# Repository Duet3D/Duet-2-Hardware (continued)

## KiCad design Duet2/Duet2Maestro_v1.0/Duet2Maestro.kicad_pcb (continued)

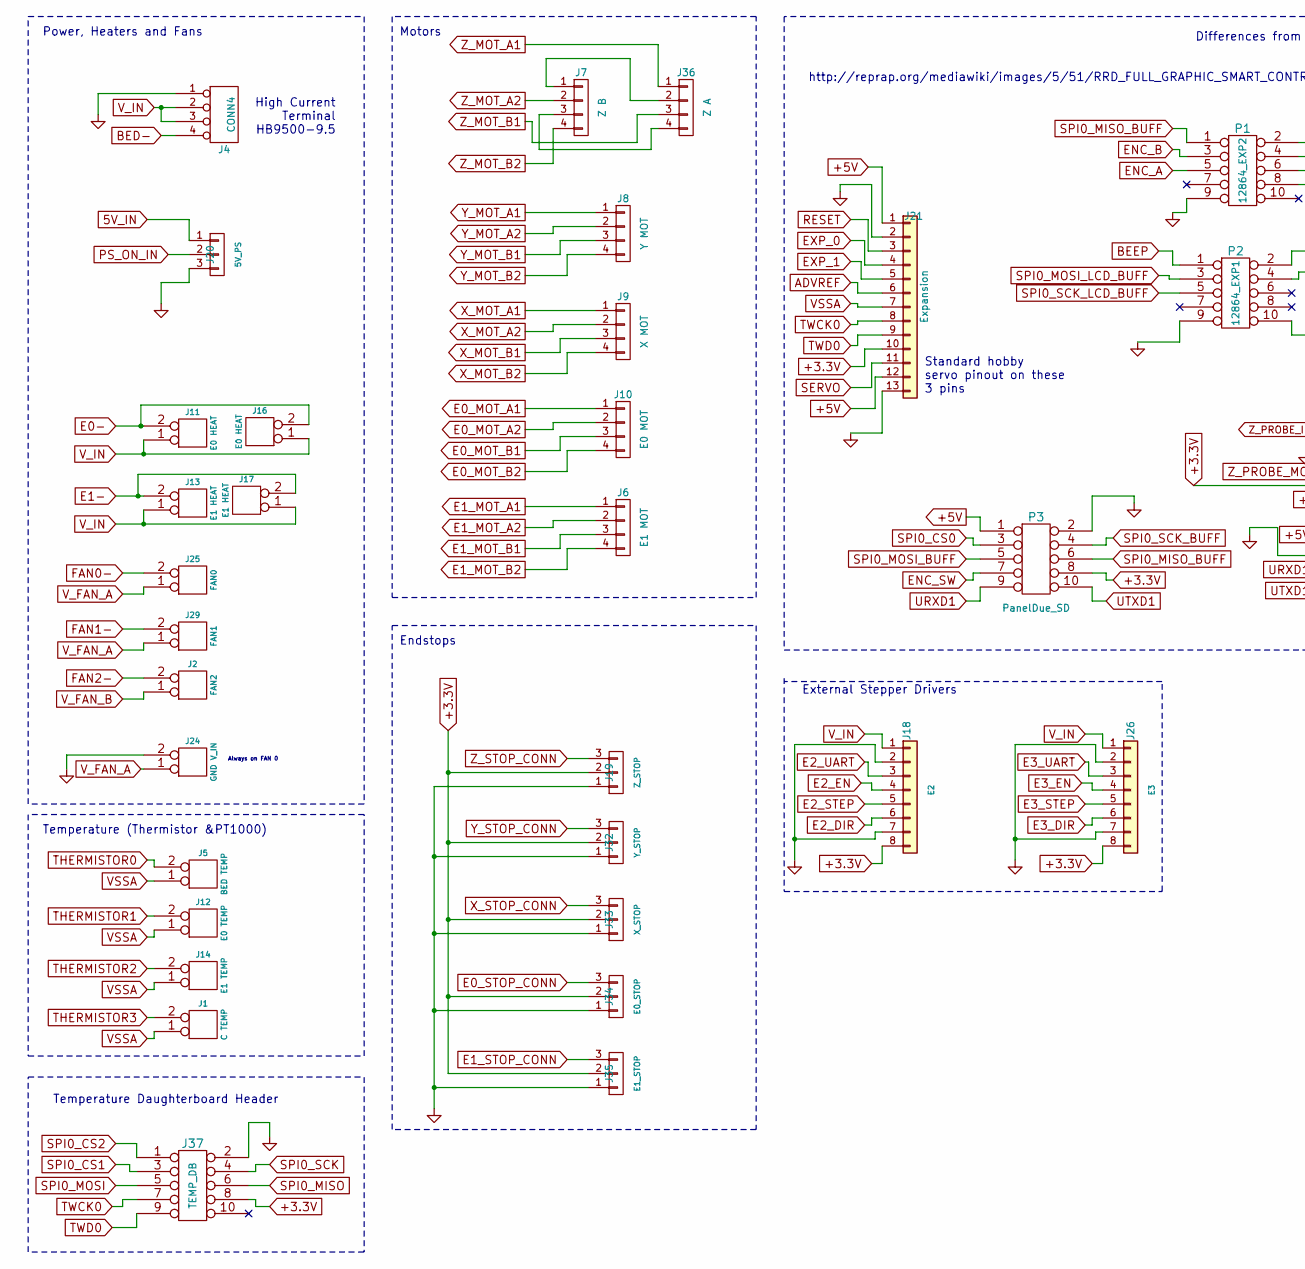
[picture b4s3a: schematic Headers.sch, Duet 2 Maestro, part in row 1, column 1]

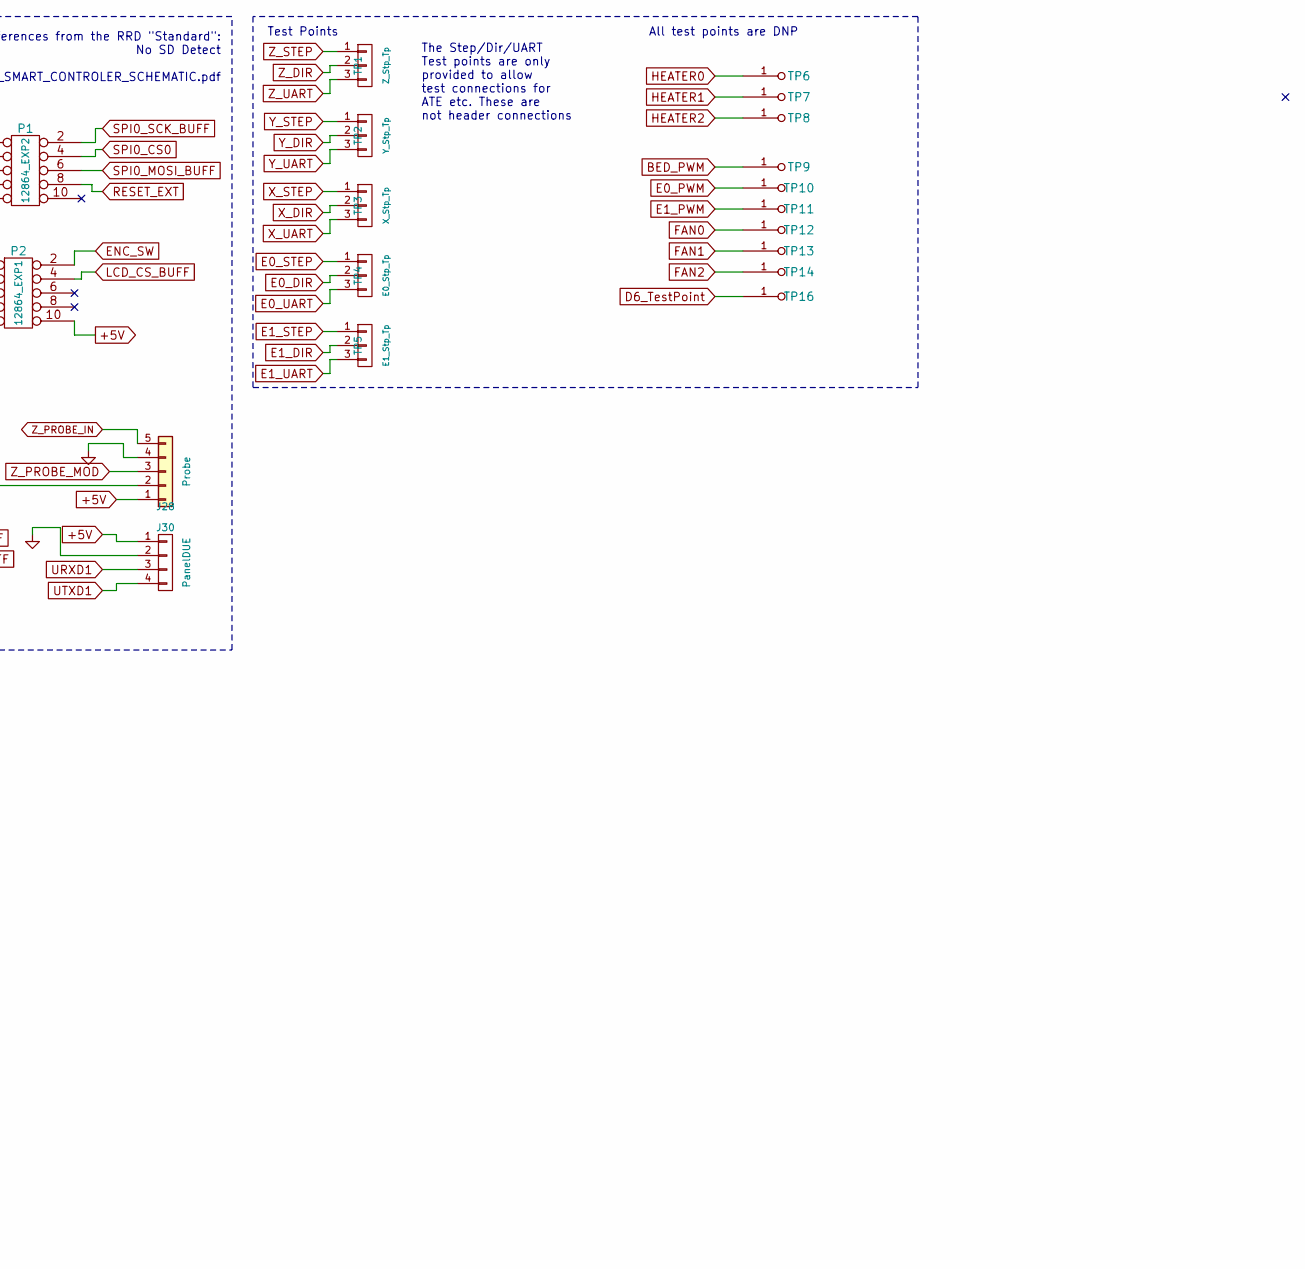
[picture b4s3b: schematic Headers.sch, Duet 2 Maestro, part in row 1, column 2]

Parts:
J1: C TEMP; PIN_ARRAY_2X1
J2: FAN2; PIN_ARRAY_2X1
J4: CONN4; screwt-barrier-9.5mm-1x4
J5: BED TEMP; PIN_ARRAY_2X1
J6: E1 MOT; PIN_ARRAY_4x1
J7: Z B; PIN_ARRAY_4x1
J8: Y MOT; PIN_ARRAY_4x1
J9: X MOT; PIN_ARRAY_4x1
J10: E0 MOT; PIN_ARRAY_4x1
J11: E0 HEAT; 3.5MM_2X1
J12: E0 TEMP; PIN_ARRAY_2X1
J13: E1 HEAT; 3.5MM_2X1
J14: E1 TEMP; PIN_ARRAY_2X1
J16: E0 HEAT; PIN_ARRAY_2X1
J17: E1 HEAT; PIN_ARRAY_2X1
J18: E2; PIN_ARRAY_8x1
J19: Z_STOP; PIN_ARRAY_3X1
J20: 5V_PS; PIN_ARRAY_3X1
J21: Expansion; Pin_Header_Straight_1x13_Pitch2.54mm
J24: GND V_IN; PIN_ARRAY_2X1
J25: FAN0; PIN_ARRAY_2X1
J26: E3; PIN_ARRAY_8x1
J28: Probe; PIN_ARRAY_5x1
J29: FAN1; PIN_ARRAY_2X1
J30: PanelDUE; PIN_ARRAY_4x1
J32: Y_STOP; PIN_ARRAY_3X1
J33: X_STOP; PIN_ARRAY_3X1
J34: E0_STOP; PIN_ARRAY_3X1
J35: E1_STOP; PIN_ARRAY_3X1
J36: Z A; PIN_ARRAY_4x1
J37: TEMP_DB; MAX_TEMP_DB
P1: 12864_EXP2; IDC_PIN_ARRAY_5x2
P2: 12864_EXP1; IDC_PIN_ARRAY_5x2
P3: PanelDue_SD; IDC_PIN_ARRAY_5x2
TP1: Z_Stp_Tp; TPx3
TP2: Y_Stp_Tp; TPx3
TP3: X_Stp_Tp; TPx3
TP4: E0_Stp_Tp; TPx3
TP5: E1_Stp_Tp; TPx3
TP6, TP7, TP8, TP9, TP10, TP11, TP12, TP13, TP14, TP16: TP; TP_via

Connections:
5V_IN: J20.1; also elsewhere on the board
+3.3V: J18.8, J19.2, J21.10, J26.8, J28.2, J32.2, J33.2, J34.2, J35.2, J37.8, P3.8; also elsewhere on the board
+5V: J21.1, J21.12, J28.1, J30.1, P2.10, P3.1; also elsewhere on the board
ADVREF: J21.6; also elsewhere on the board
BED-: J4.4; also elsewhere on the board
BED_PWM: TP9.1; also elsewhere on the board
BEEP: P2.1; also elsewhere on the board
D6_TestPoint: TP16.1; also elsewhere on the board
E0-: J11.2 (PM), J16.2 (PM); also elsewhere on the board
E0_DIR: TP4.2; also elsewhere on the board
E0_MOT_A1: J10.1; also elsewhere on the board
E0_MOT_A2: J10.2; also elsewhere on the board
E0_MOT_B1: J10.3; also elsewhere on the board
E0_MOT_B2: J10.4; also elsewhere on the board
E0_PWM: TP10.1; also elsewhere on the board
E0_STEP: TP4.1; also elsewhere on the board
E0_STOP_CONN: J34.3; also elsewhere on the board
E0_UART: TP4.3; also elsewhere on the board
E1-: J13.2 (PM), J17.2 (PM); also elsewhere on the board
E1_DIR: TP5.2; also elsewhere on the board
E1_MOT_A1: J6.1; also elsewhere on the board
E1_MOT_A2: J6.2; also elsewhere on the board
E1_MOT_B1: J6.3; also elsewhere on the board
E1_MOT_B2: J6.4; also elsewhere on the board
E1_PWM: TP11.1; also elsewhere on the board
E1_STEP: TP5.1; also elsewhere on the board
E1_STOP_CONN: J35.3; also elsewhere on the board
E1_UART: TP5.3; also elsewhere on the board
E2_DIR: J18.6; also elsewhere on the board
E2_EN: J18.4; also elsewhere on the board
E2_STEP: J18.5; also elsewhere on the board
E2_UART: J18.3; also elsewhere on the board
E3_DIR: J26.6; also elsewhere on the board
E3_EN: J26.4; also elsewhere on the board
E3_STEP: J26.5; also elsewhere on the board
E3_UART: J26.3; also elsewhere on the board
ENC_A: P1.5; also elsewhere on the board
ENC_B: P1.3; also elsewhere on the board
ENC_SW: P2.2, P3.7; also elsewhere on the board
EXP_0: J21.4; also elsewhere on the board
EXP_1: J21.5; also elsewhere on the board
FAN0: TP12.1; also elsewhere on the board
FAN0-: J25.2 (PM); also elsewhere on the board
FAN1: TP13.1; also elsewhere on the board
FAN1-: J29.2 (PM); also elsewhere on the board
FAN2: TP14.1; also elsewhere on the board
FAN2-: J2.2 (PM); also elsewhere on the board
GND: J4.1, J18.2, J18.7, J19.1, J20.3, J21.2, J21.13, J24.2 (PM), J26.2, J26.7, J28.4, J30.2, J32.1, J33.1, J34.1, J35.1, J37.2, P1.9, P2.9, P3.2; also elsewhere on the board
HEATER0: TP6.1; also elsewhere on the board
HEATER1: TP7.1; also elsewhere on the board
HEATER2: TP8.1; also elsewhere on the board
LCD_CS_BUFF: P2.4; also elsewhere on the board
unnamed: J7.1, J36.2
unnamed: J7.3, J36.4
PS_ON_IN: J20.2; also elsewhere on the board
RESET: J21.3; also elsewhere on the board
RESET_EXT: P1.8; also elsewhere on the board
SERVO: J21.11; also elsewhere on the board
SPI0_CS0: P1.4, P3.3; also elsewhere on the board
SPI0_CS1: J37.3; also elsewhere on the board
SPI0_CS2: J37.1; also elsewhere on the board
SPI0_MISO: J37.6; also elsewhere on the board
SPI0_MISO_BUFF: P1.1, P3.6; also elsewhere on the board
SPI0_MOSI: J37.5; also elsewhere on the board
SPI0_MOSI_BUFF: P1.6, P3.5; also elsewhere on the board
SPI0_MOSI_LCD_BUFF: P2.3; also elsewhere on the board
SPI0_SCK: J37.4; also elsewhere on the board
SPI0_SCK_BUFF: P1.2, P3.4; also elsewhere on the board
SPI0_SCK_LCD_BUFF: P2.5; also elsewhere on the board
THERMISTOR0: J5.2 (PM); also elsewhere on the board
THERMISTOR1: J12.2 (PM); also elsewhere on the board
THERMISTOR2: J14.2 (PM); also elsewhere on the board
THERMISTOR3: J1.2 (PM); also elsewhere on the board
TWCK0: J21.8, J37.7; also elsewhere on the board
TWD0: J21.9, J37.9; also elsewhere on the board
URXD1: J30.3, P3.9; also elsewhere on the board
UTXD1: J30.4, P3.10; also elsewhere on the board
VSSA: J1.1, J5.1, J12.1, J14.1, J21.7; also elsewhere on the board
V_FAN_A: J24.1, J25.1, J29.1; also elsewhere on the board
V_FAN_B: J2.1; also elsewhere on the board
V_IN: J4.2, J4.3, J11.1, J13.1, J16.1, J17.1, J18.1, J26.1; also elsewhere on the board
X_DIR: TP3.2; also elsewhere on the board
X_MOT_A1: J9.1; also elsewhere on the board
X_MOT_A2: J9.2; also elsewhere on the board
X_MOT_B1: J9.3; also elsewhere on the board
X_MOT_B2: J9.4; also elsewhere on the board
X_STEP: TP3.1; also elsewhere on the board
X_STOP_CONN: J33.3; also elsewhere on the board
X_UART: TP3.3; also elsewhere on the board
Y_DIR: TP2.2; also elsewhere on the board
Y_MOT_A1: J8.1; also elsewhere on the board
Y_MOT_A2: J8.2; also elsewhere on the board
Y_MOT_B1: J8.3; also elsewhere on the board
Y_MOT_B2: J8.4; also elsewhere on the board
Y_STEP: TP2.1; also elsewhere on the board
Y_STOP_CONN: J32.3; also elsewhere on the board
Y_UART: TP2.3; also elsewhere on the board
Z_DIR: TP1.2; also elsewhere on the board
Z_MOT_A1: J36.1; also elsewhere on the board
Z_MOT_A2: J7.2; also elsewhere on the board
Z_MOT_B1: J36.3; also elsewhere on the board
Z_MOT_B2: J7.4; also elsewhere on the board
Z_PROBE_IN: J28.5; also elsewhere on the board
Z_PROBE_MOD: J28.3; also elsewhere on the board
Z_STEP: TP1.1; also elsewhere on the board
Z_STOP_CONN: J19.3; also elsewhere on the board
Z_UART: TP1.3; also elsewhere on the board

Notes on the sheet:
High Current Terminal HB9500-9.5
Always on FAN 0
Power, Heaters and Fans
Temperature (Thermistor &PT1000)
Motors
Endstops
Test Points
All test points are DNP
The Step/Dir/UART Test points are only provided to allow test connections for ATE etc. These are not header connections
Differences from the RRD "Standard": No SD Detect http://reprap.org/mediawiki/images/5/51/RRD_FULL_GRAPHIC_SMART_CONTROLER_SCHEMATIC.pdf
Standard hobby servo pinout on these 3 pins
Temperature Daughterboard Header
External Stepper Drivers

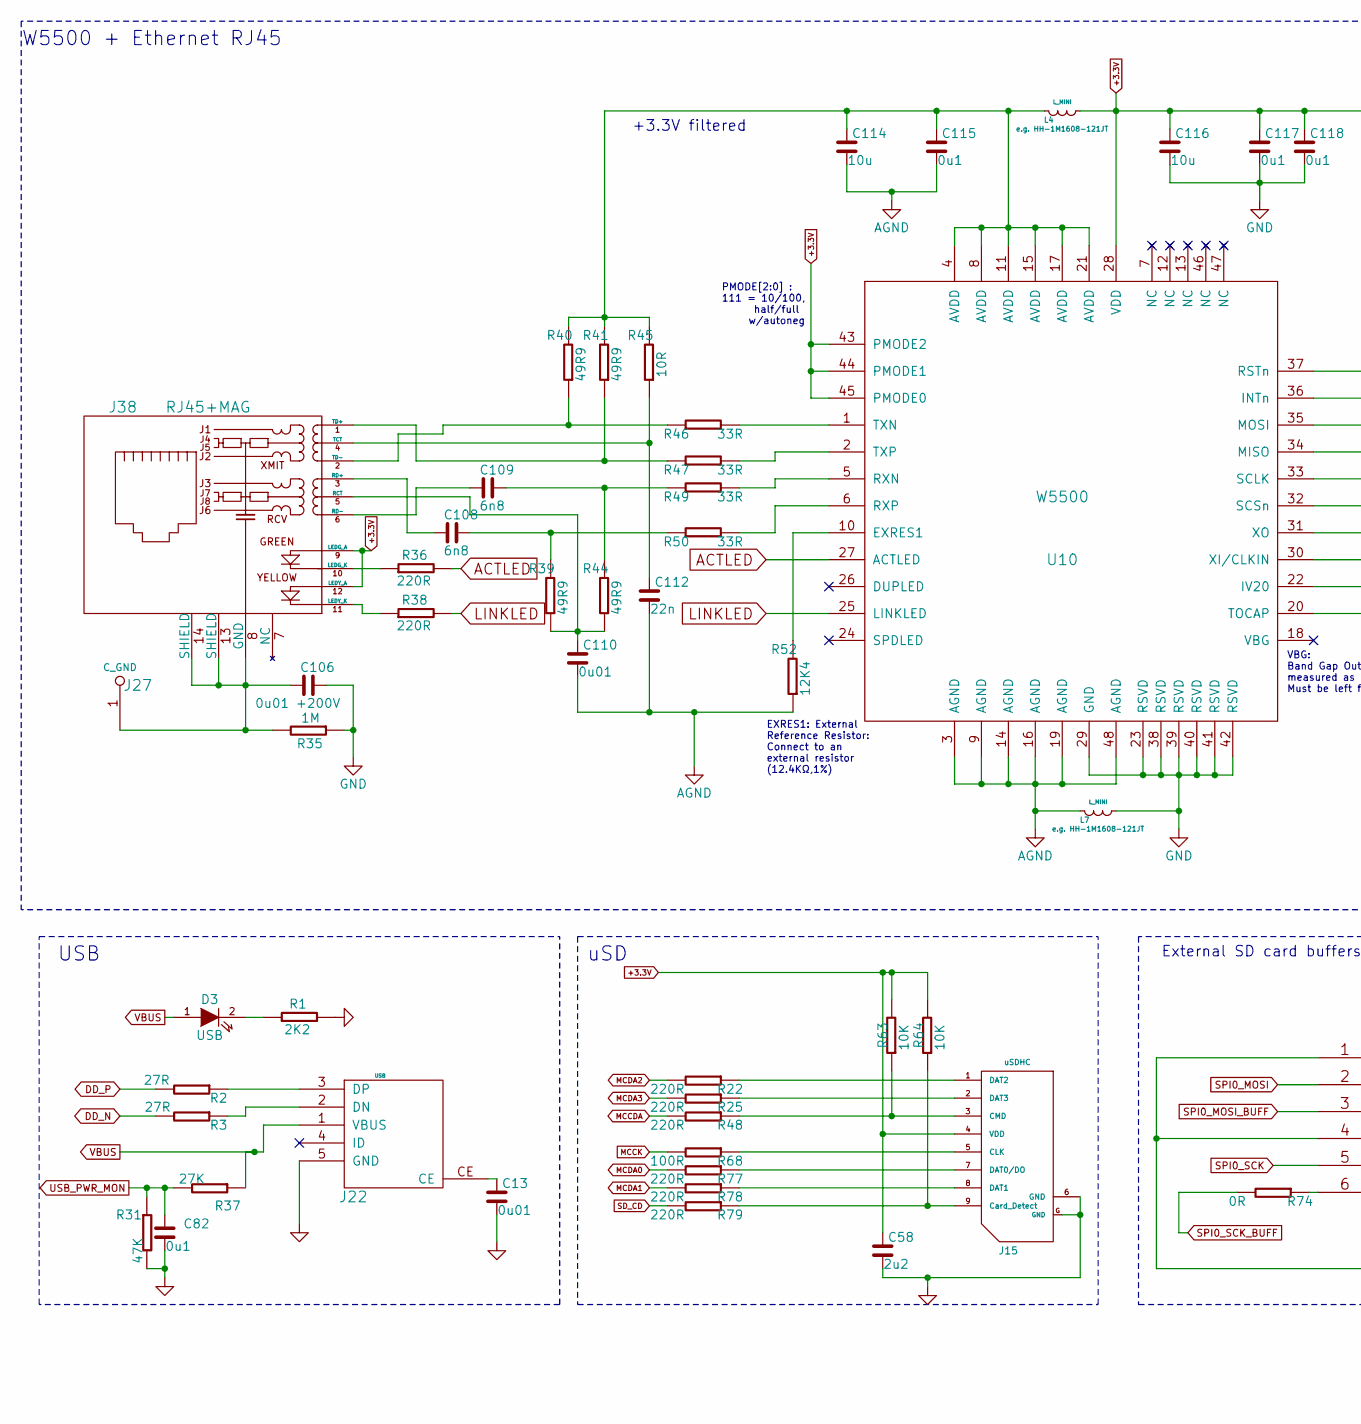
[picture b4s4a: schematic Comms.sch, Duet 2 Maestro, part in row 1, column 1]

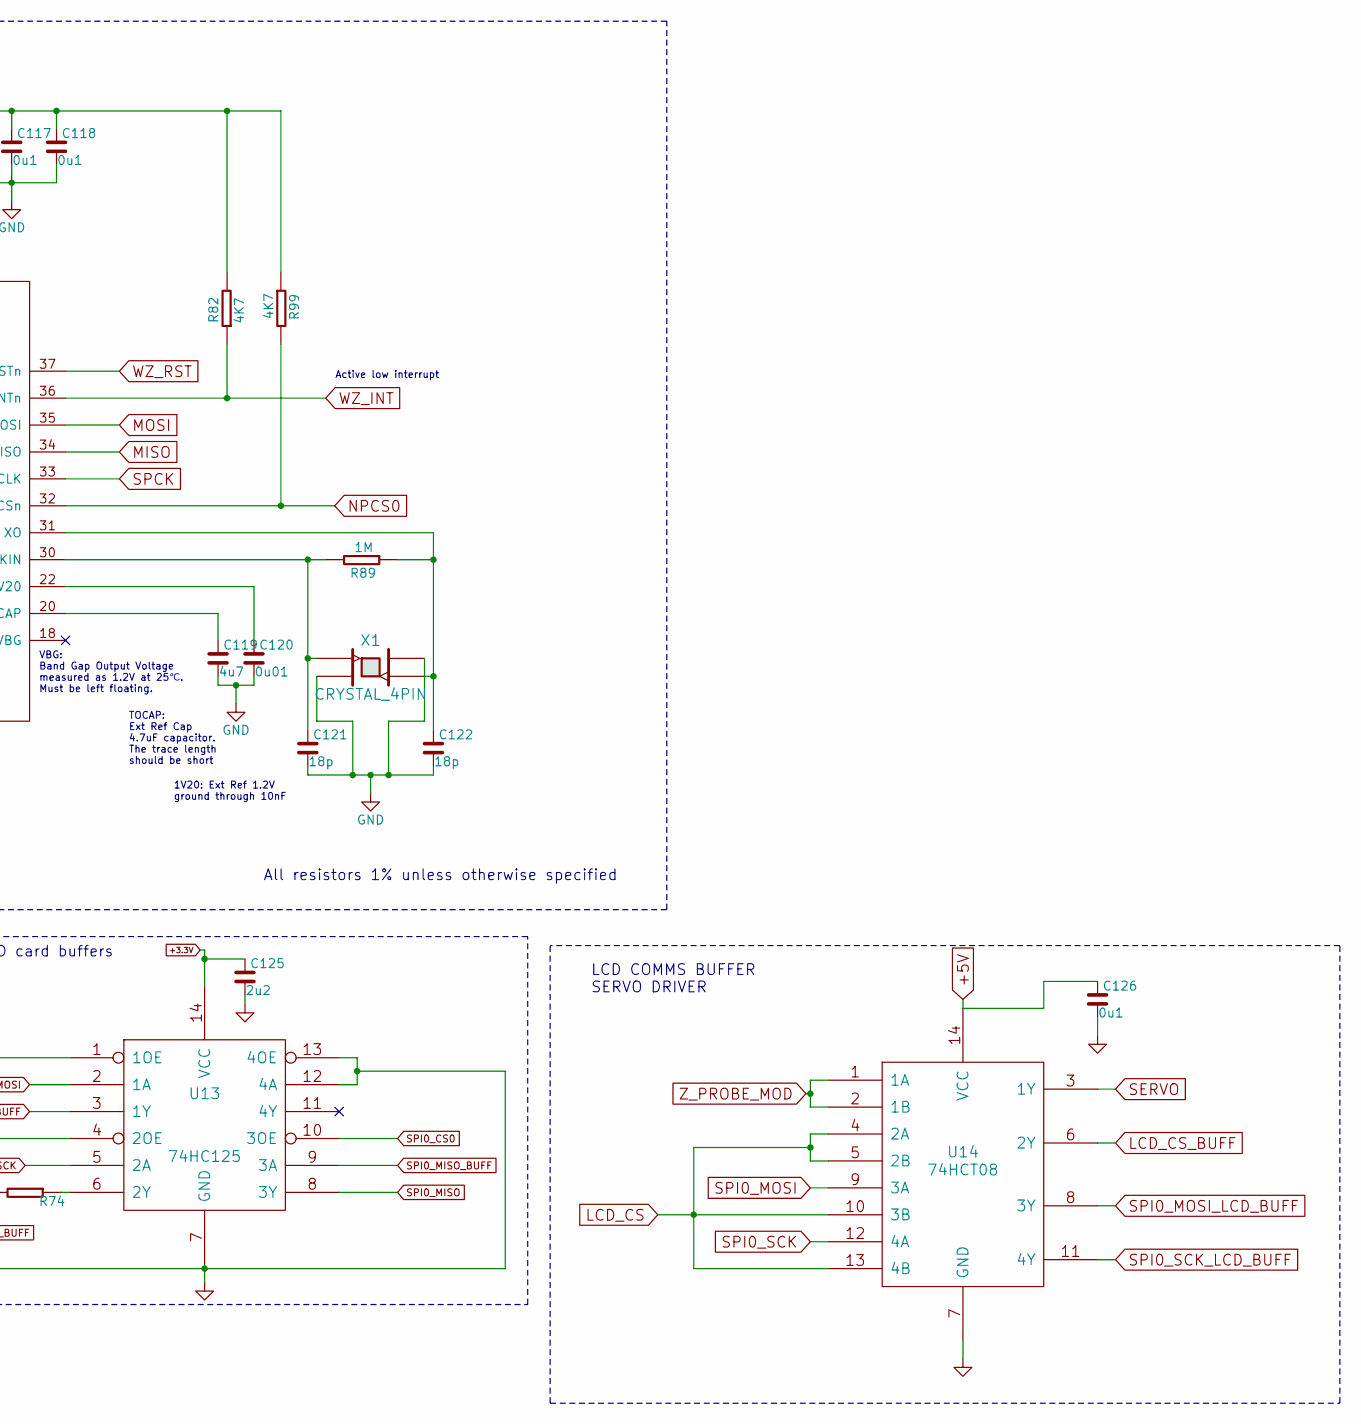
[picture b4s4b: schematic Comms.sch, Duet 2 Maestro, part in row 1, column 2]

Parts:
C13, C110, C120: 0u01; C_0603
C58, C125: 2u2; C_0603
C82, C115, C117, C118, C126: 0u1; C_0603
C106: 0u01 +200V; C_0603
C108, C109: 6n8; C_0603
C112: 22n; C_0603
C114, C116: 10u; C_0805
C119: 4u7; C_0805
C121, C122: 18p; C_0603
D3: USB; D_0603
J15: uSDHC; uSD_SKT
J22: USB; uUSB_new
J27: C_GND; 2.8mm_Spade_terminal
J38: RJ45+MAG
L4, L7: L_MINI; R_0603
R1: 2K2; R_0603
R2, R3: 27R; R_0603
R22, R25, R36, R38, R48, R77, R78, R79: 220R; R_0603
R31: 47K; R_0603
R35, R89: 1M; R_0603
R37: 27K; R_0603
R39, R40, R41, R44: 49R9; R_0603
R45: 10R; R_0603
R46, R47, R49, R50: 33R; R_0603
R52: 12K4; R_0603
R63, R64: 10K; R_0603
R68: 100R; R_0603
R74: 0R; R_0603
R82, R99: 4K7; R_0603
U10: W5500; LQFP-48_7x7mm_Pitch0.5mm
U13: 74HC125; TSSOP-14
U14: 74HCT08; TSSOP-14
X1: CRYSTAL_4PIN; Xtal_5x3.2

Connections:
+3.3V: C58.1, C116.1, C117.1, C118.1, C125.1, J15.4 (VDD), J38.9 (LEDG_A), J38.12 (LEDY_A), L4.2 (B), R63.2, R64.2, R82.2, R99.1, U10.28 (VDD), U10.43 (PMODE2), U10.44 (PMODE1), U10.45 (PMODE0), U13.14 (VCC); also elsewhere on the board
+5V: C126.1, U14.14 (VCC); also elsewhere on the board
ACTLED: R36.2, U10.27 (ACTLED)
AGND: C110.2, C112.2, C114.2, C115.2, L7.1 (A), R52.1, U10.3 (AGND), U10.9 (AGND), U10.14 (AGND), U10.16 (AGND), U10.19 (AGND), U10.48 (AGND)
DD_N: R3.2; also elsewhere on the board
DD_P: R2.2; also elsewhere on the board
GND: C13.2, C58.2, C82.2, C106.1, C116.2, C117.2, C118.2, C119.2, C120.2, C121.2, C122.2, C125.2, C126.2, J15.6 (GND), J15.G (GND), J22.5 (GND), L7.2 (B), R1.2, R31.2, R35.1, U10.23 (RSVD), U10.29 (GND), U10.38 (RSVD), U10.39 (RSVD), U10.40 (RSVD), U10.41 (RSVD), U10.42 (RSVD), U13.1 (1OE), U13.4 (2OE), U13.7 (GND), U13.12 (4A), U13.13 (4OE), U14.7 (GND), X1.2, X1.4; also elsewhere on the board
LCD_CS: U14.4 (2A), U14.5 (2B), U14.10 (3B), U14.13 (4B); also elsewhere on the board
LCD_CS_BUFF: U14.6 (2Y); also elsewhere on the board
LINKLED: R38.2, U10.25 (LINKLED)
MCCDA: R48.2; also elsewhere on the board
MCCK: R68.2; also elsewhere on the board
MCDA0: R77.2; also elsewhere on the board
MCDA1: R78.2; also elsewhere on the board
MCDA2: R22.2; also elsewhere on the board
MCDA3: R25.2; also elsewhere on the board
MISO: U10.34 (MISO); also elsewhere on the board
MOSI: U10.35 (MOSI); also elsewhere on the board
NPCS0: R99.2, U10.32 (SCSn); also elsewhere on the board
unnamed: C13.1, J22.CE
unnamed: C106.2, J27.1, J38.8 (GND), J38.13 (SHIELD), J38.14 (SHIELD), R35.2
unnamed: C108.1, R39.2, R50.1
unnamed: C108.2, J38.3 (RD+)
unnamed: C109.1, R44.2, R49.1
unnamed: C109.2, J38.6 (RD-)
unnamed: C110.1, J38.5 (RCT), R39.1, R44.1
unnamed: C112.1, J38.4 (TCT), R45.1
unnamed: C114.1, C115.1, L4.1 (A), R40.2, R41.2, R45.2, U10.4 (AVDD), U10.8 (AVDD), U10.11 (AVDD), U10.15 (AVDD), U10.17 (AVDD), U10.21 (AVDD)
unnamed: C119.1, U10.20 (TOCAP)
unnamed: C120.1, U10.22 (IV20)
unnamed: C121.1, R89.2, U10.30 (XI/CLKIN), X1.1
unnamed: C122.1, R89.1, U10.31 (XO), X1.3
unnamed: D3.2 (K), R1.1
unnamed: J15.1 (DAT2), R22.1
unnamed: J15.2 (DAT3), R25.1
unnamed: J15.3 (CMD), R48.1, R63.1
unnamed: J15.5 (CLK), R68.1
unnamed: J15.7 (DAT0/DO), R77.1
unnamed: J15.8 (DAT1), R78.1
unnamed: J15.9 (Card_Detect), R64.1, R79.1
unnamed: J22.2 (DN), R3.1
unnamed: J22.3 (DP), R2.1
unnamed: J38.1 (TD+), R41.1, R47.1
unnamed: J38.2 (TD-), R40.1, R46.1
unnamed: J38.10 (LEDG_K), R36.1
unnamed: J38.11 (LEDY_K), R38.1
unnamed: R46.2, U10.1 (TXN)
unnamed: R47.2, U10.2 (TXP)
unnamed: R49.2, U10.5 (RXN)
unnamed: R50.2, U10.6 (RXP)
unnamed: R52.2, U10.10 (EXRES1)
unnamed: R74.1, U13.6 (2Y)
SD_CD: R79.2; also elsewhere on the board
SERVO: U14.3 (1Y); also elsewhere on the board
SPCK: U10.33 (SCLK); also elsewhere on the board
SPI0_CS0: U13.10 (3OE); also elsewhere on the board
SPI0_MISO: U13.8 (3Y); also elsewhere on the board
SPI0_MISO_BUFF: U13.9 (3A); also elsewhere on the board
SPI0_MOSI: U13.2 (1A), U14.9 (3A); also elsewhere on the board
SPI0_MOSI_BUFF: U13.3 (1Y); also elsewhere on the board
SPI0_MOSI_LCD_BUFF: U14.8 (3Y); also elsewhere on the board
SPI0_SCK: U13.5 (2A), U14.12 (4A); also elsewhere on the board
SPI0_SCK_BUFF: R74.2; also elsewhere on the board
SPI0_SCK_LCD_BUFF: U14.11 (4Y); also elsewhere on the board
USB_PWR_MON: C82.1, R31.1, R37.2; also elsewhere on the board
VBUS: D3.1 (A), J22.1 (VBUS), R37.1; also elsewhere on the board
WZ_INT: R82.1, U10.36 (INTn); also elsewhere on the board
WZ_RST: U10.37 (RSTn); also elsewhere on the board
Z_PROBE_MOD: U14.1 (1A), U14.2 (1B); also elsewhere on the board

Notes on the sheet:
uSD
W5500 + Ethernet RJ45
USB
All resistors 1% unless otherwise specified
PMODE[2:0] : 111 = 10/100, half/full w/autoneg
EXRES1: External Reference Resistor: Connect to an external resistor (12.4KΩ,1%)
VBG: Band Gap Output Voltage measured as 1.2V at 25℃. Must be left floating.
TOCAP: Ext Ref Cap 4.7uF capacitor. The trace length should be short
1V20: Ext Ref 1.2V ground through 10nF
Active low interrupt
External SD card buffers
LCD COMMS BUFFER SERVO DRIVER
+3.3V filtered

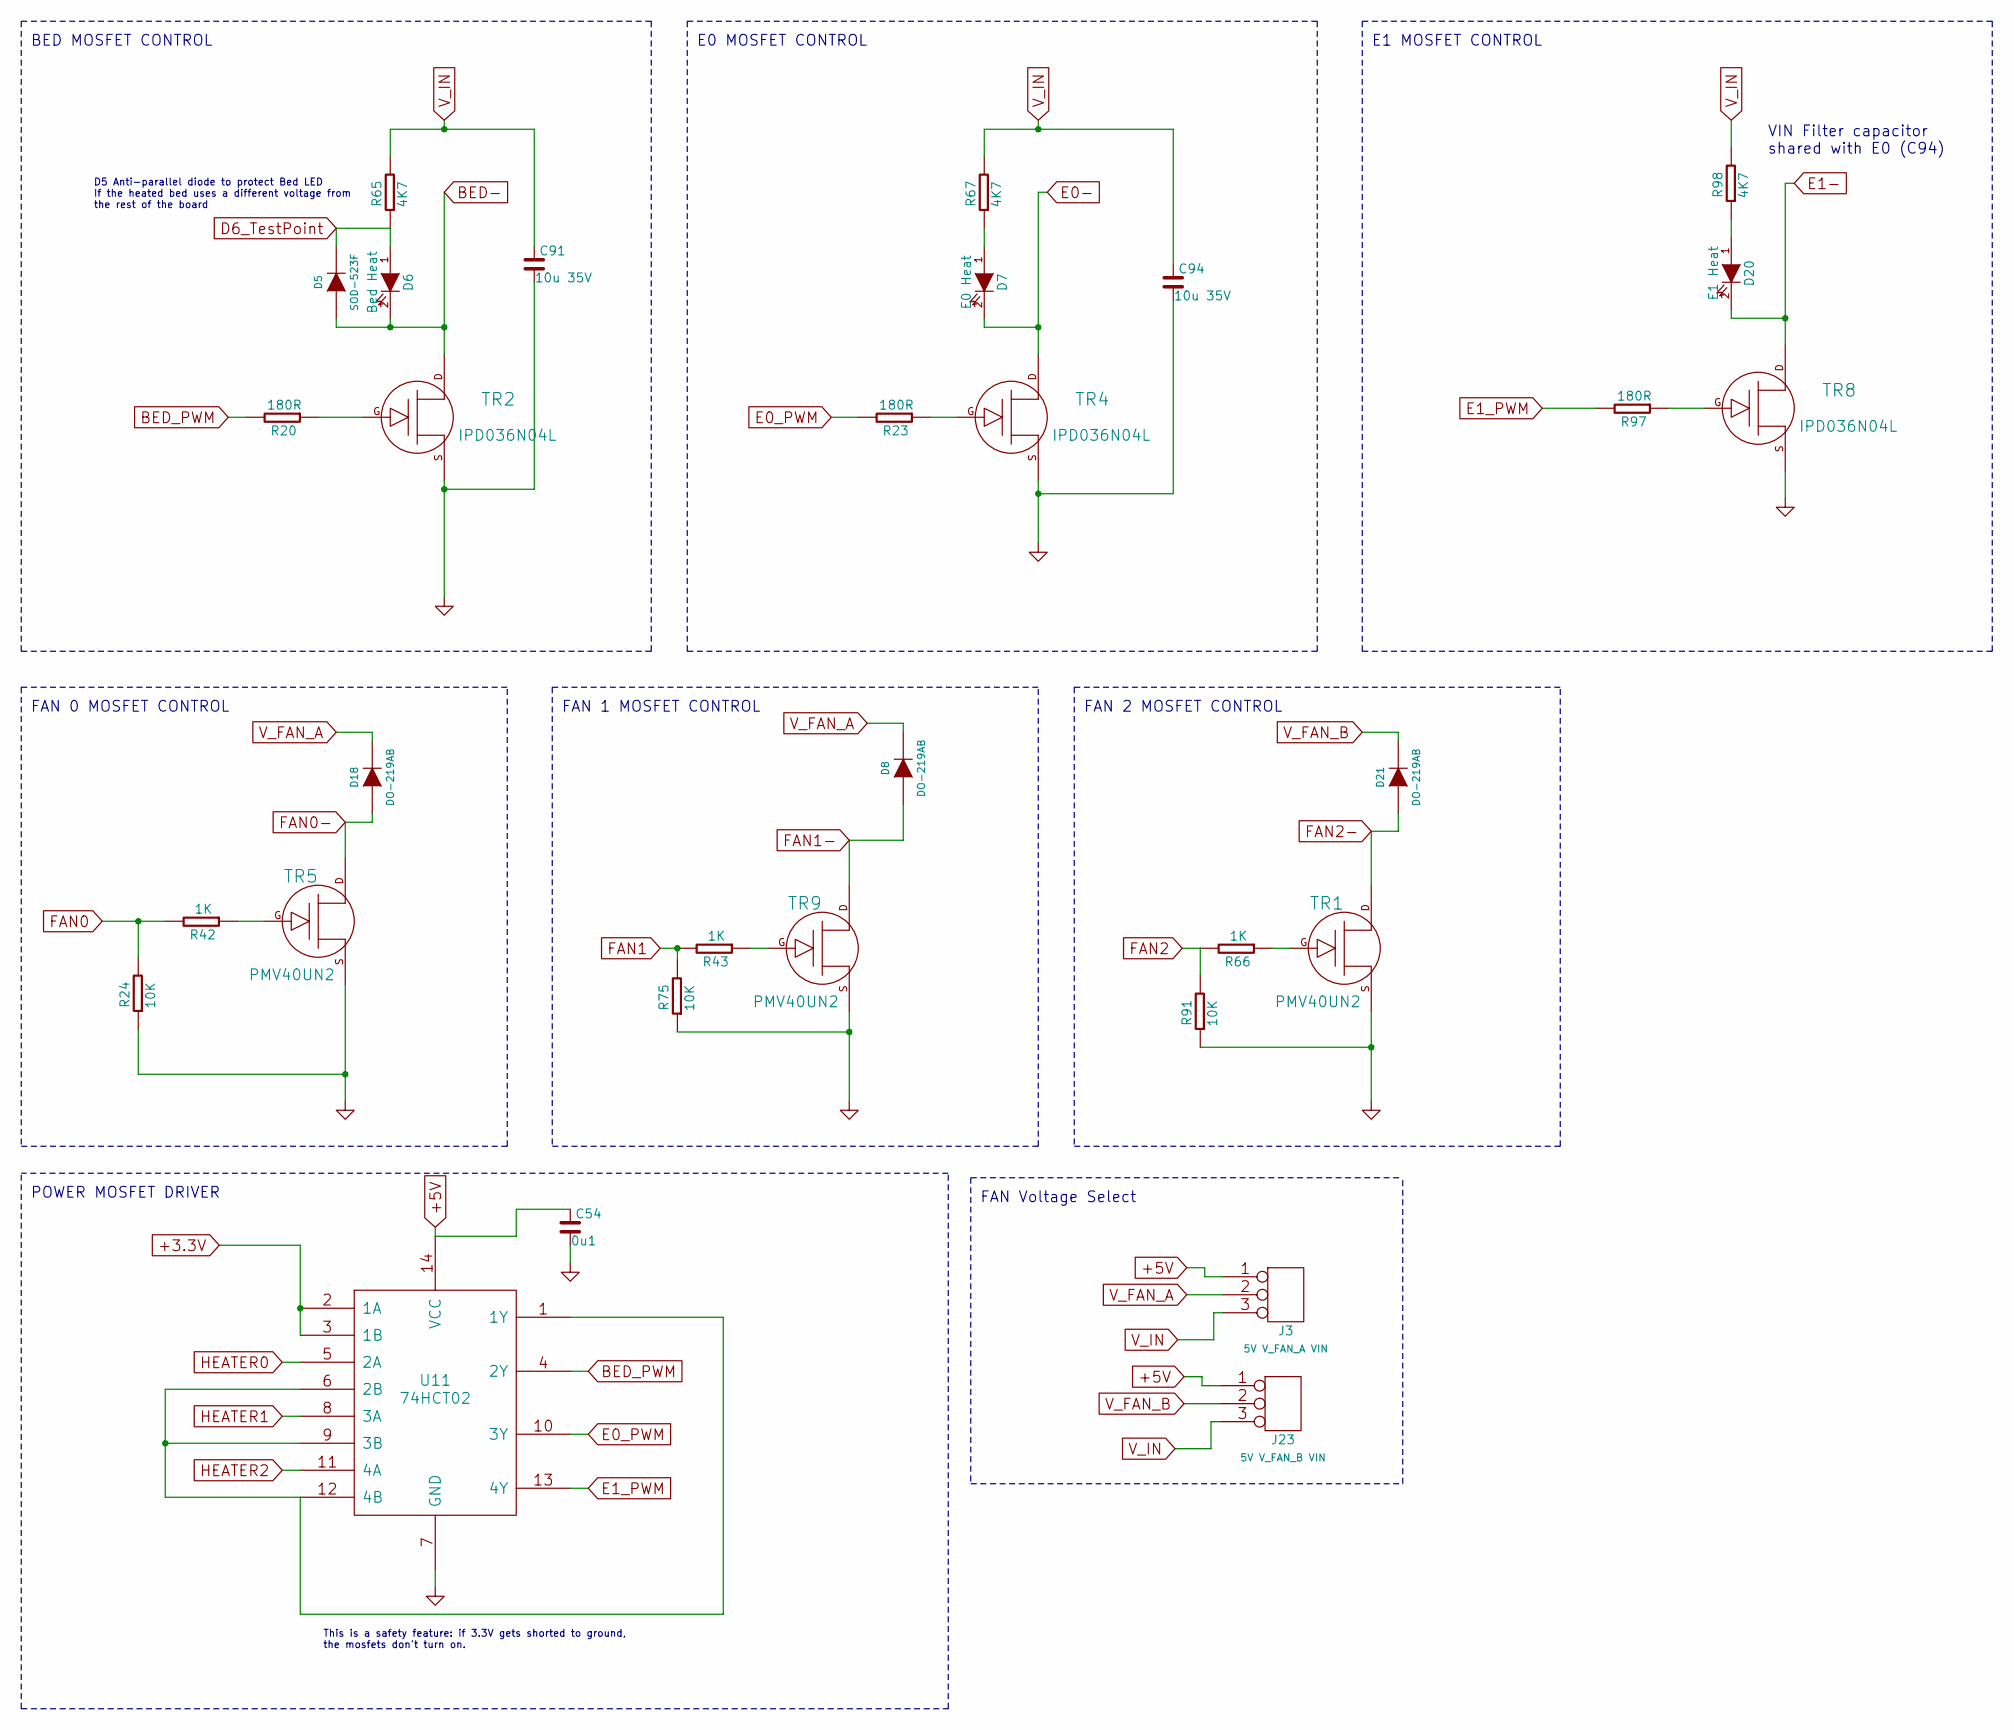
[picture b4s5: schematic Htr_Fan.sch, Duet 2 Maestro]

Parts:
C54: 0u1; C_0603
C91, C94: 10u 35V; C_1206
D5: SOD-523F
D6: Bed Heat; D_0603
D7: E0 Heat; D_0603
D8, D18, D21: DO-219AB
D20: E1 Heat; D_0603
J3: 5V V_FAN_A VIN; CONN_3x1
J23: 5V V_FAN_B VIN; CONN_3x1
R20, R23, R97: 180R; R_0603
R24, R75, R91: 10K; R_0603
R42, R43, R66: 1K; R_0603
R65, R67, R98: 4K7; R_0603
TR1, TR5, TR9: PMV40UN2; SOT-23
TR2, TR4, TR8: IPD036N04L; D-PAK
U11: 74HCT02; TSSOP-14

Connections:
+3.3V: U11.2 (1A), U11.3 (1B); also elsewhere on the board
+5V: C54.1, J3.1, J23.1, U11.14 (VCC); also elsewhere on the board
BED-: D5.2 (A), D6.2 (K), TR2.D; also elsewhere on the board
BED_PWM: R20.2, U11.4 (2Y); also elsewhere on the board
D6_TestPoint: D5.1 (K), D6.1 (A), R65.1; also elsewhere on the board
E0-: D7.2 (K), TR4.D; also elsewhere on the board
E0_PWM: R23.2, U11.10 (3Y); also elsewhere on the board
E1-: D20.2 (K), TR8.D; also elsewhere on the board
E1_PWM: R97.2, U11.13 (4Y); also elsewhere on the board
FAN0: R24.2, R42.2; also elsewhere on the board
FAN0-: D18.2 (A), TR5.D; also elsewhere on the board
FAN1: R43.2, R75.2; also elsewhere on the board
FAN1-: D8.2 (A), TR9.D; also elsewhere on the board
FAN2: R66.2, R91.2; also elsewhere on the board
FAN2-: D21.2 (A), TR1.D; also elsewhere on the board
GND: C54.2, C91.2, C94.2, R24.1, R75.1, R91.1, TR1.S, TR2.S, TR4.S, TR5.S, TR8.S, TR9.S, U11.7 (GND); also elsewhere on the board
HEATER0: U11.5 (2A); also elsewhere on the board
HEATER1: U11.8 (3A); also elsewhere on the board
HEATER2: U11.11 (4A); also elsewhere on the board
unnamed: D7.1 (A), R67.1
unnamed: D20.1 (A), R98.1
unnamed: R20.1, TR2.G
unnamed: R23.1, TR4.G
unnamed: R42.1, TR5.G
unnamed: R43.1, TR9.G
unnamed: R66.1, TR1.G
unnamed: R97.1, TR8.G
unnamed: U11.1 (1Y), U11.6 (2B), U11.9 (3B), U11.12 (4B)
V_FAN_A: D8.1 (K), D18.1 (K), J3.2 (PM); also elsewhere on the board
V_FAN_B: D21.1 (K), J23.2 (PM); also elsewhere on the board
V_IN: C91.1, C94.1, J3.3, J23.3, R65.2, R67.2, R98.2; also elsewhere on the board

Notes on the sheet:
FAN 0 MOSFET CONTROL
E0 MOSFET CONTROL
BED MOSFET CONTROL
E1 MOSFET CONTROL
FAN 1 MOSFET CONTROL
POWER MOSFET DRIVER
This is a safety feature: if 3.3V gets shorted to ground, the mosfets don't turn on.
FAN 2 MOSFET CONTROL
D5 Anti-parallel diode to protect Bed LED If the heated bed uses a different voltage from the rest of the board
FAN Voltage Select
VIN Filter capacitor shared with E0 (C94)
